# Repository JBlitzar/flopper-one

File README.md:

# flopper-one

I built an open source Flipper Zero clone from scratch for a sixth of the cost.

[☞ How this got built](docs/journey.md)

Flopper One is a handheld security research tool built on an ESP32. It can send and receive IR signals, interface with NFC and RFID tags, scan for BLE devices, and run WiFi attacks — all from a d-pad and a 240x240 LCD. It fits in a pocket.

The Flipper Zero costs $200 + $60 for the WiFi add-on. Flopper One's full BOM comes to **$30.38**. The only missing features are sub-GHz radio (easily added) and iButton (pretty niche).

<table width="100%">
    <tr>
        <td>
            
        </td>
        <td>
            
        </td>
    </tr>
</table>

## Schematic, PCB

## BOM

| Item                      | Link                                                               | Unit Cost | Qty |      Total |
| ------------------------- | ------------------------------------------------------------------ | --------: | --: | ---------: |
| ESP32 WROOM               | [AliExpress](https://www.aliexpress.us/item/3256805942117284.html) |     $4.71 |   1 |      $4.71 |
| TSOP38238 (IR receiver)   | [LCSC C141632](https://www.lcsc.com/product-detail/C141632.html)   |     $0.73 |   1 |      $0.73 |
| TSAL6200 (IR emitter)     | [LCSC C55528](https://www.lcsc.com/product-detail/C55528.html)     |     $0.83 |   1 |      $0.83 |
| PN532 (NFC/RFID)          | [AliExpress](https://www.aliexpress.us/item/3256806254348567.html) |     $0.99 |   1 |      $0.99 |
| ST7789 240×240 LCD        | [AliExpress](https://www.aliexpress.us/item/2255799995721426.html) |     $3.57 |   1 |      $3.57 |
| B3F tactile switches (x5) | [LCSC C271750](https://www.lcsc.com/product-detail/C271750.html)   |     $1.07 |   1 |      $1.07 |
| 2N2222A transistor        | [LCSC C118536](https://www.lcsc.com/product-detail/C118536.html)   |     $0.77 |   1 |      $0.77 |
| 1 kΩ resistors            | —                                                                  |      free |   3 |          — |
| 47–100 Ω resistors        | —                                                                  |      free |   1 |          — |
| 10 µF capacitors          | —                                                                  |      free |   2 |          — |
| Power switch              | —                                                                  |      free |   1 |          — |
| Header pins               | —                                                                  |      free |   — |          — |
| LCSC shipping             | —                                                                  |         — |   — |     $11.21 |
| PCBs (JLCPCB, min qty 5)  | —                                                                  |         — |   — |      $6.50 |
| **Total**                 |                                                                    |           |     | **$30.38** |

## How to use

Plug the esp into your computer and flash the firmware in /firmware using [platformIO](https://docs.platformio.org/en/latest/core/quickstart.html) in vscode. Use the d-pad to navigate.

See more in [firmware/README.md](firmware/README.md) !

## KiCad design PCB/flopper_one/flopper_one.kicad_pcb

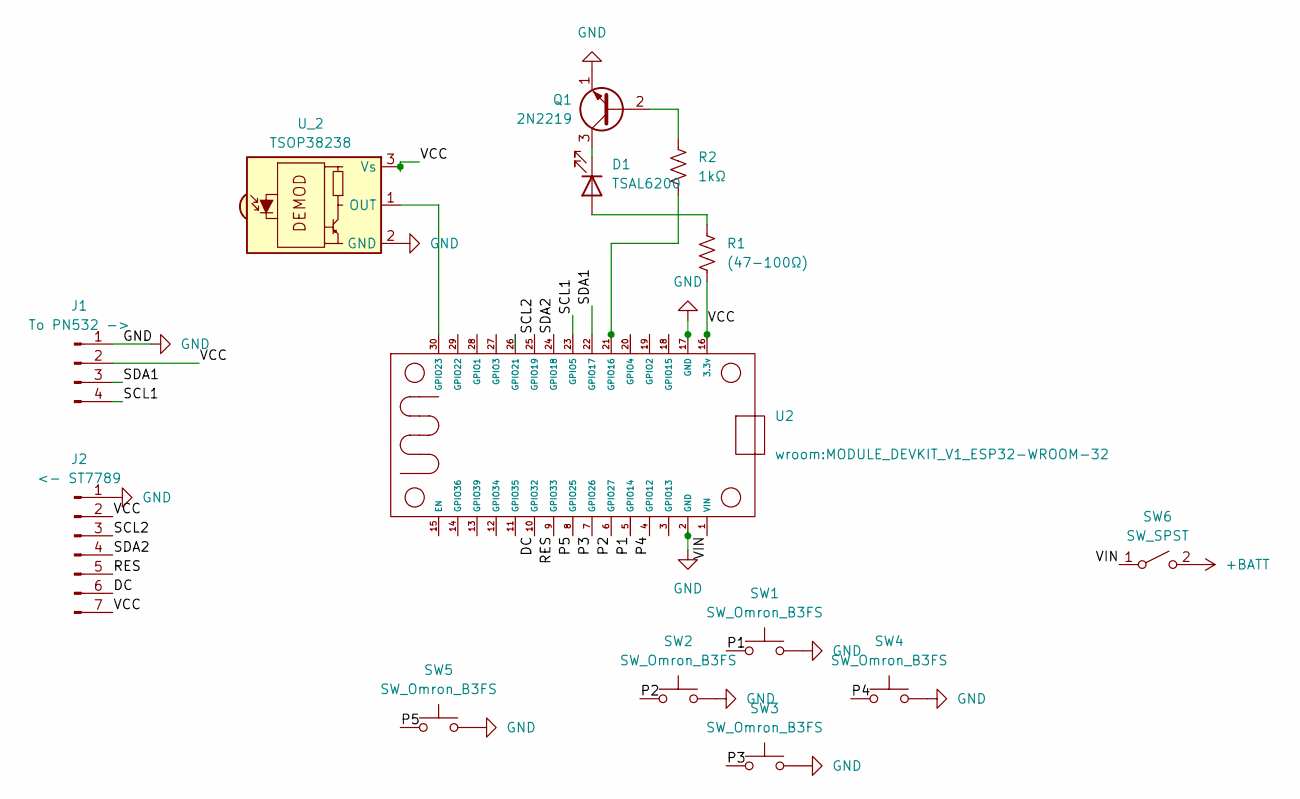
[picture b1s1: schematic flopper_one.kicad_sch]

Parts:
D1: TSAL6200; LED_D5.0mm_IRBlack
J1: To PN532 ->; PinHeader_1x04_P2.54mm_Vertical
J2: <- ST7789; PinHeader_1x07_P2.54mm_Vertical
Q1: 2N2219; TO-39-3
R1: (47-100Ω); R_Axial_DIN0207_L6.3mm_D2.5mm_P7.62mm_Horizontal
R2: 1kΩ; R_Axial_DIN0207_L6.3mm_D2.5mm_P7.62mm_Horizontal
SW1, SW2, SW3, SW4, SW5: SW_Omron_B3FS; SW_SPST_Omron_B3FS-100xP
SW6: SW_SPST; my_switch
U2: MODULE_DEVKIT_V1_ESP32-WROOM-32
U_2: TSOP38238; Vishay_MINICAST-3Pin

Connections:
+BATT: SW6.2 (B)
/DC: J2.6, U2.10 (GPIO32)
/P1: SW1.1, U2.5 (GPIO14)
/P2: SW2.1, U2.6 (GPIO27)
/P3: SW3.1, U2.7 (GPIO26)
/P4: SW4.1, U2.4 (GPIO12)
/P5: SW5.1, U2.8 (GPIO25)
/RES: J2.5, U2.9 (GPIO33)
/SCL1: J1.4 (GND), U2.23 (GPIO5)
/SCL2: J2.3, U2.25 (GPIO19)
/SDA1: J1.3 (TX), U2.22 (GPIO17)
/SDA2: J2.4, U2.24 (GPIO18)
/VCC: J1.2 (RX), J2.2, J2.7, R1.2, U2.16 (3.3v), U_2.3 (Vs)
/VIN: SW6.1 (A), U2.1 (VIN)
GND: J1.1 (VCC), J2.1, Q1.1 (E), SW1.2, SW2.2, SW3.2, SW4.2, SW5.2, U2.2 (GND), U2.17 (GND), U_2.2 (GND)
unnamed: D1.2 (A), R1.1
unnamed: D1.1 (K), Q1.3 (C)
unnamed: Q1.2 (B), R2.1
unnamed: R2.2, U2.21 (GPIO16)
unnamed: U2.30 (GPIO23), U_2.1 (OUT)

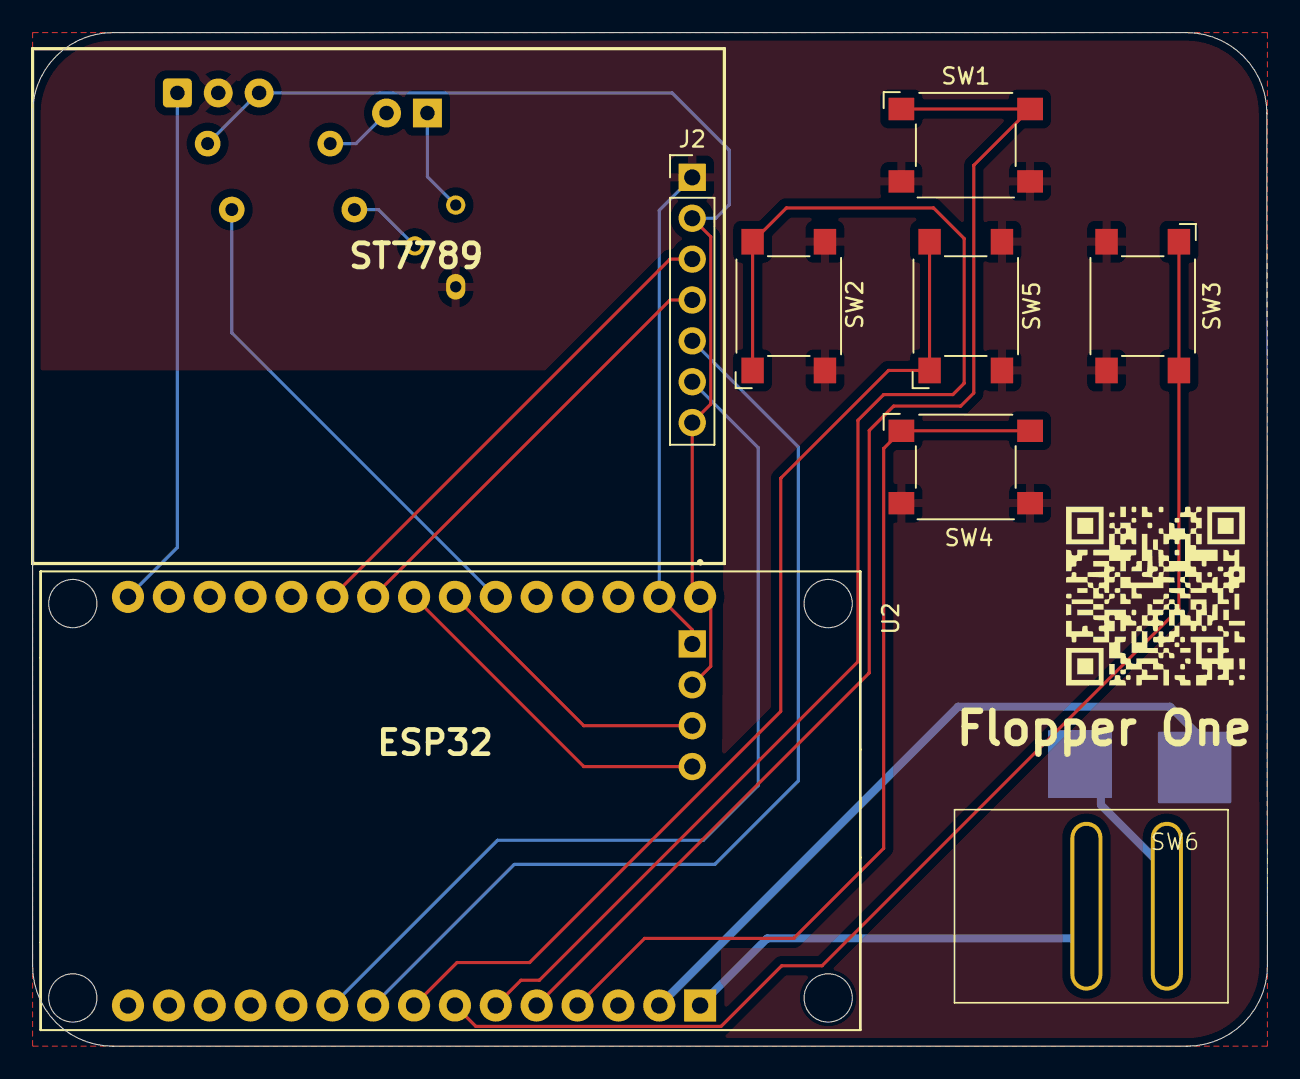
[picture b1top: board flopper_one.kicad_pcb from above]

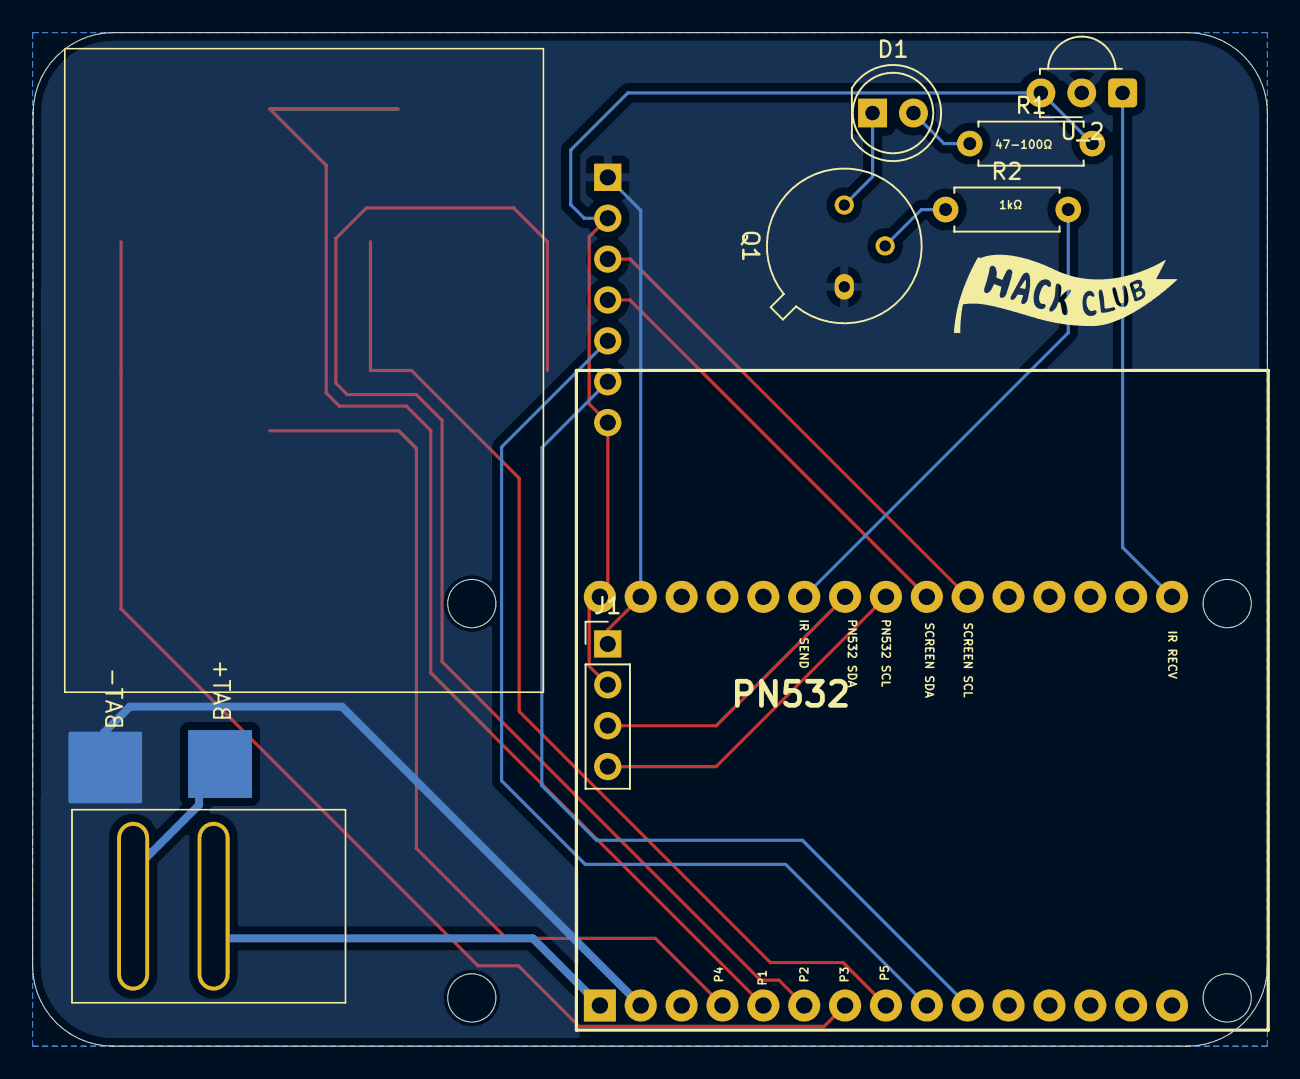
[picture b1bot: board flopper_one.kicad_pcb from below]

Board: 2 copper layers, 76.8 x 63.0 mm, 14 parts (6 on the bottom side), 19 nets.

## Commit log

2026-02-06 asdf
2026-02-06 adfsdfd
2026-02-06 last
2026-02-06 routed switches
2026-02-06 start routing ir
2026-02-07 use labels
2026-02-07 routed the pcb
2026-02-07 shipping from us
2026-02-07 add battery
2026-02-08 added like power circuits fr
2026-02-08 fix battery rq
2026-02-08 clean stuff up
2026-02-08 add nice 3d models
2026-02-08 platformio init
2026-02-08 self test ?
2026-02-08 pn532 test
2026-02-08 basic works
2026-02-08 remove stupid stuff from self test
    works on my esp trust
2026-02-08 pinset I guess
2026-02-08 remove dep fallbacks
2026-02-08 gerbers, bom
2026-02-08 cad folder
2026-02-08 lowk wrote the readme
2026-02-08 asdfasf
2026-02-08 afsd
2026-02-08 asdfa
2026-02-08 fix minor error
2026-02-08 asfd
2026-02-08 move stuff around
2026-02-09 uhm fix drc errors
2026-02-09 shove cap again
2026-02-09 yum yum clean traces
2026-02-09 labelss
2026-02-09 "quick" schematic fix
2026-02-09 update bom
2026-02-09 flip r6
2026-02-09 afsdafsd
2026-02-09 gerber cicd
2026-02-09 dril
2026-02-10 pretty pictures
2026-02-10 make thicker and add gnd pour
2026-02-11 adfadfds
2026-02-11 free shipping
2026-02-11 rm that one resistor + gnd pour
2026-02-11 make more things thicker
2026-02-11 visual
2026-02-12 ad st7789
2026-02-12 update blender
2026-02-12 better render
2026-02-12 step
2026-02-12 checklist
2026-02-12 asdffdsafsadiuhfwaafwhoirugahiuwgr
2026-02-17 display is spi oops
2026-02-17 edit steps
2026-02-17 better 3d model
2026-02-20 better materials
2026-02-20 redo renders
2026-02-20 better scripty
2026-02-20 the ultimate blender CI I guess
2026-02-20 yesh
2026-02-20 experimental
2026-02-20 "just use the vias"
2026-02-22 rounded corners
2026-02-22 rm old files
2026-02-27 cosmetic pcb changes
2026-02-27 blendeoawihrower
2026-03-04 inputss
2026-03-04 menunode, app
2026-03-04 menu manager
2026-03-04 proper ui
2026-03-04 apps
2026-03-04 main only
2026-03-04 avoid breadcrumb realloc
2026-03-05 menu
2026-03-05 wifi
2026-03-05 better emit
2026-03-05 sour
2026-03-05 sink ap
2026-03-05 ble test app
2026-03-06 final gerbers...
2026-03-07 pn532 et al
2026-03-16 cope
2026-03-17 Initial plan
2026-03-18 simplify a bunch because reordering pcb
2026-03-18 order it
2026-03-18 docs, menu
2026-03-18 bigger menu
2026-03-18 funny desktop preview, some ui tweaks
2026-03-18 semantic colors
2026-03-19 breadcru bs
2026-03-20 redme
2026-04-08 idk atp bor
2026-04-14 221 21
2026-04-14 Revert "221 21"
    This reverts commit 874aac615fa746419b686e9dd117baf88c943263.
2026-04-15 Revert "Update tft_espi_setup.h"
    This reverts commit 7c41c03ec66cde922960aec06c67519122e50c42.
2026-04-15 Revert "idk atp bor"
    This reverts commit f192c50f8d14fa0c8f00f94e7ebd811e34cebf83.
2026-04-15 clanker ports, works now
2026-04-15 dirty tracking
2026-04-15 correct pins
2026-04-23 adfs
